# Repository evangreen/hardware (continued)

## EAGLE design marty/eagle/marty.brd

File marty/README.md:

# Marty McFly

The Marty McFly was a set of boards I created in late 2015 for my girlfriend as a gift. It's an LED countdown clock, in the style of the console from "Back to the Future". The three displays track the programmable "destination time" on the top row, the current time on the bottom row, and the "estimated time to arrival" in the middle row. The destination time and current time can be programmed using the keypad. The ETA counts up if the current time is after the destination time.

### Motivation
Because it's fun. I was hoping to give this to my girlfriend in time for the Back to the Future anniversary, but failed to complete it in time. She still appreciated the gift, and she ended up making the cool backing and framing for it.

I also wanted a chance to play with the HT16K33 chip, which drives a matrix of LEDs with constant current, and can simultaneously scan in a matrix keypad. It interfaces with a microcontroller via I2C.

### Sourcing
I wanted attractive LEDs and a retro keypad for this project. It seems like most of the cheap 7-segment displays being sold now have rectangular bars for the top and bottom segments. I prefer the more symmetric face where all segments have the pointy ends that join with each other. This led me toward the older HDSP LEDs that HP used to make. I also needed a consistent look across three colors: red, yellow and green. It took some doing, but I eventually found sets of LEDs in each color with the front face I wanted. I also stumbled across somebody selling old touchtone phone keypads on eBay, which seemed perfect for this project. Once I had my LEDs, I could start designing the board.

### Hardware Design
I used Seeedstudio to make my boards. They are incredibly cheap, but it takes awhile for the boards to get back to you, and you must buy quantities of at least 5. Rather than making one very large board (which would have been very expensive), or two different types of small boards, I wanted to send away for a single PCB design that could serve multiple purposes, depending on which parts were populated.

Each row in the display is actually two boards side by side, with holes for LEDs in a 2-2-4 digit combination. For the date version on the left, all LEDs are populated, and for the time on the right, the last two digits of the year are left unpopulated.

Most of the boards are simply display boards. Pins on the left pipe I2C commands directly into the HT16K33, and pins on the right forward those commands out to the next board. One board also has an ATMega on it, this is the master board that controls all the other display boards. Of course, the design is the same, so all boards have the traces and pads for the ATMega, but only one has it populated. One board also has the keypad connected to it (though again, the keypad pins are there on every board). I used solder bridge "parts" in the PCB design, then blobbed solder bridges in unique binary combinations to give each board a different I2C ID.

### Firwmare Design
The firmware on the ATMega needs to keep track of the current date and time, store a destination time, calculate the delta between them, and display all three of these values by sending them out to the displays via I2C. It also needs to poll for changes on the keypad, and allow for programming of either the current time or the destination time.

Tracking time is always tricky business. Computing the difference between two calendar dates can also be very tricky, especially when considering changes like Daylight Saving transitions and computing a delta in terms of months and days.

Internally I store time as a tuple of Year, Day (of year), and Second (of day). Storing it this way means I can add and subtract time easily, and only worry about things like Daylight Saving when it's time to display something. Advancing the time is done by adding to the seconds, then calling a normalize function to make sure seconds, days, and year are all within a valid range. The number of seconds per day is always constant (since we adjust for Daylight Saving later), and the number of days in a year is either 365 or 366 depending on the year.

Converting a DATE into a full calendar date involves dealing with Daylight Saving, then splitting out the fields. We compute the Day-of-Year on which the Daylight Saving transitions occur for the given year, and see whether or not our day and time fall within that range. If they do, we add another hour to the seconds and re-normalize. Splitting Day-of-Year into Month and Day is a short loop of subtracting the number of days for each month while possible. Splitting the seconds into hours, minutes, and seconds is simple division.

Computing the difference between dates reuses a lot of the same logic. The delta itself is computed by subtracting each field from its counterpart (ie LeftSeconds - RightSeconds, LeftDays - RightDays, LeftYears - RightYears), and then calling the same normalize and display routines as before. The benefit of this is that the ETA counter will always tick down consistently, even across Daylight Saving transitions. The slight downside is it means the first "month" difference between two dates is always the number of days in January, even if two dates in question are something February 1st and March 1st. This seemed like a decent tradeoff, since it allowed a lot of code reuse and kept the countdown consistent, at the cost of intuitive but sometimes ambiguous month delta results.

### Results
Great success! The project came together smoothly, and my girlfriend did an amazing job with the fit and finish of the display. I was overall quite happy with the HT16K33 chips, they made controlling a large number of LEDs and interfacing with the keypad very simple. The green 7-segment HDSP displays I got on eBay are weaker than I'd like. They are a bit dim, and I can see a ripple from the asymmetric multiplexing of the HT16K33 (since some time slots go to the keypad). I blame the LEDs for this more than the HT16K33, since the symptoms appear isolated to the green LEDs. The yellow LEDs, which are actually newer and came from Lite-On, are my favorite, as they're clear and bright.

I would use the HT16K33 again in future projects. It might be a bit expensive in production, but for small hobby projects like mine it does a great job freeing up the MCU and cutting down on PCB traces. I wish I had used it in the Airlight project.

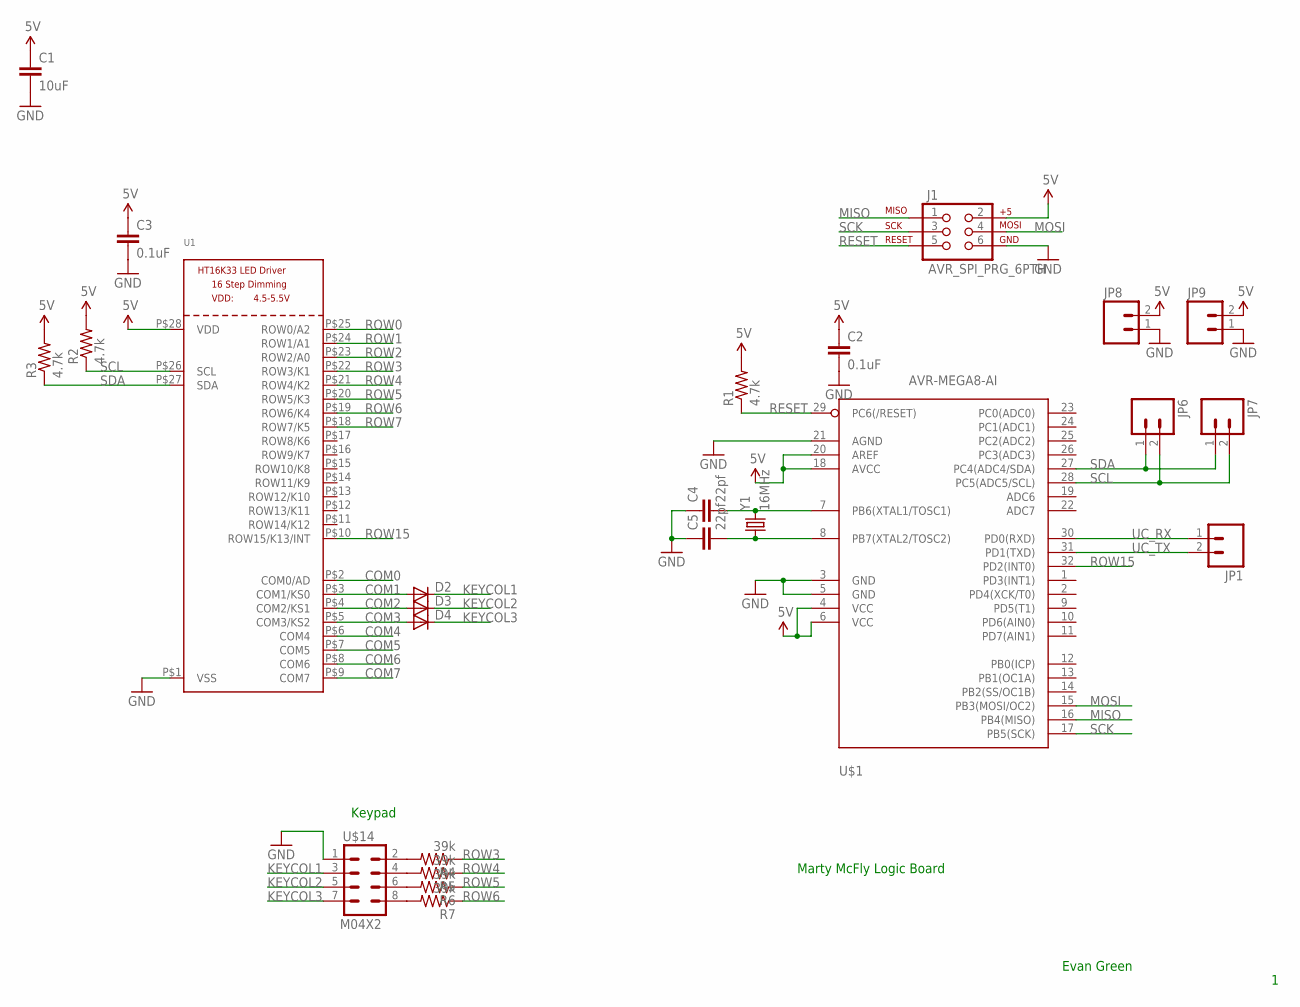
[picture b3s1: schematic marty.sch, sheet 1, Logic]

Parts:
C1: 10uF; 1210
C2, C3: 0.1uF; 0402-CAP
C4, C5: 22pf; 0402-CAP
D2, D3, D4: DIODESOD; SOD-323
J1: AVR_SPI_PRG_6PTH; 2X3
JP1, JP6, JP7, JP8, JP9: M02PTH; 1X02
R1, R2, R3: 4.7k; 0402-RES
R4, R5, R6, R7: 39k; 0402-RES
U1: HT16K33_SOP28; SOP28_300MIL
U$1: AVR-MEGA8-AI; TQFP32-08
U$14: M04X2; 2X4
Y1: 16MHz; HC49US

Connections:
5V: C1.1, C2.1, C3.1, J1.2, JP8.2, JP9.2, R1.2, R2.2, R3.2, U1.P$28 (VDD), U$1.4 (VCC), U$1.6 (VCC), U$1.18 (AVCC), U$1.20 (AREF)
COM0: U1.P$2 (COM0/AD); also elsewhere on the board
COM1: D2.2 (A), U1.P$3 (COM1/KS0); also elsewhere on the board
COM2: D3.2 (A), U1.P$4 (COM2/KS1); also elsewhere on the board
COM3: D4.2 (A), U1.P$5 (COM3/KS2); also elsewhere on the board
COM4: U1.P$6 (COM4); also elsewhere on the board
COM5: U1.P$7 (COM5); also elsewhere on the board
COM6: U1.P$8 (COM6); also elsewhere on the board
COM7: U1.P$9 (COM7); also elsewhere on the board
GND: C1.2, C2.2, C3.2, C4.1, C5.1, J1.6, JP8.1, JP9.1, U1.P$1 (VSS), U$1.3 (GND), U$1.5 (GND), U$1.21 (AGND), U$14.1
KEYCOL1: D2.1 (C), U$14.3
KEYCOL2: D3.1 (C), U$14.5
KEYCOL3: D4.1 (C), U$14.7
MISO: J1.1, U$1.16 (PB4(MISO))
MOSI: J1.4, U$1.15 (PB3(MOSI/OC2))
unnamed: C4.2, U$1.7 (PB6(XTAL1/TOSC1)), Y1.2
unnamed: C5.2, U$1.8 (PB7(XTAL2/TOSC2)), Y1.1
unnamed: R4.2, U$14.2
unnamed: R5.2, U$14.4
unnamed: R6.2, U$14.6
unnamed: R7.2, U$14.8
RESET: J1.5, R1.1, U$1.29 (PC6(/RESET))
ROW0: U1.P$25 (ROW0/A2); also elsewhere on the board
ROW1: U1.P$24 (ROW1/A1); also elsewhere on the board
ROW2: U1.P$23 (ROW2/A0); also elsewhere on the board
ROW3: R4.1, U1.P$22 (ROW3/K1); also elsewhere on the board
ROW4: R5.1, U1.P$21 (ROW4/K2); also elsewhere on the board
ROW5: R6.1, U1.P$20 (ROW5/K3); also elsewhere on the board
ROW6: R7.1, U1.P$19 (ROW6/K4); also elsewhere on the board
ROW7: U1.P$18 (ROW7/K5); also elsewhere on the board
ROW15: U1.P$10 (ROW15/K13/INT), U$1.32 (PD2(INT0))
SCK: J1.3, U$1.17 (PB5(SCK))
SCL: JP6.2, JP7.2, R2.1, U1.P$26 (SCL), U$1.28 (PC5(ADC5/SCL))
SDA: JP6.1, JP7.1, R3.1, U1.P$27 (SDA), U$1.27 (PC4(ADC4/SDA))
UC_RX: JP1.1, U$1.30 (PD0(RXD))
UC_TX: JP1.2, U$1.31 (PD1(TXD))

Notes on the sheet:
Marty McFly Logic Board
Evan Green
Keypad

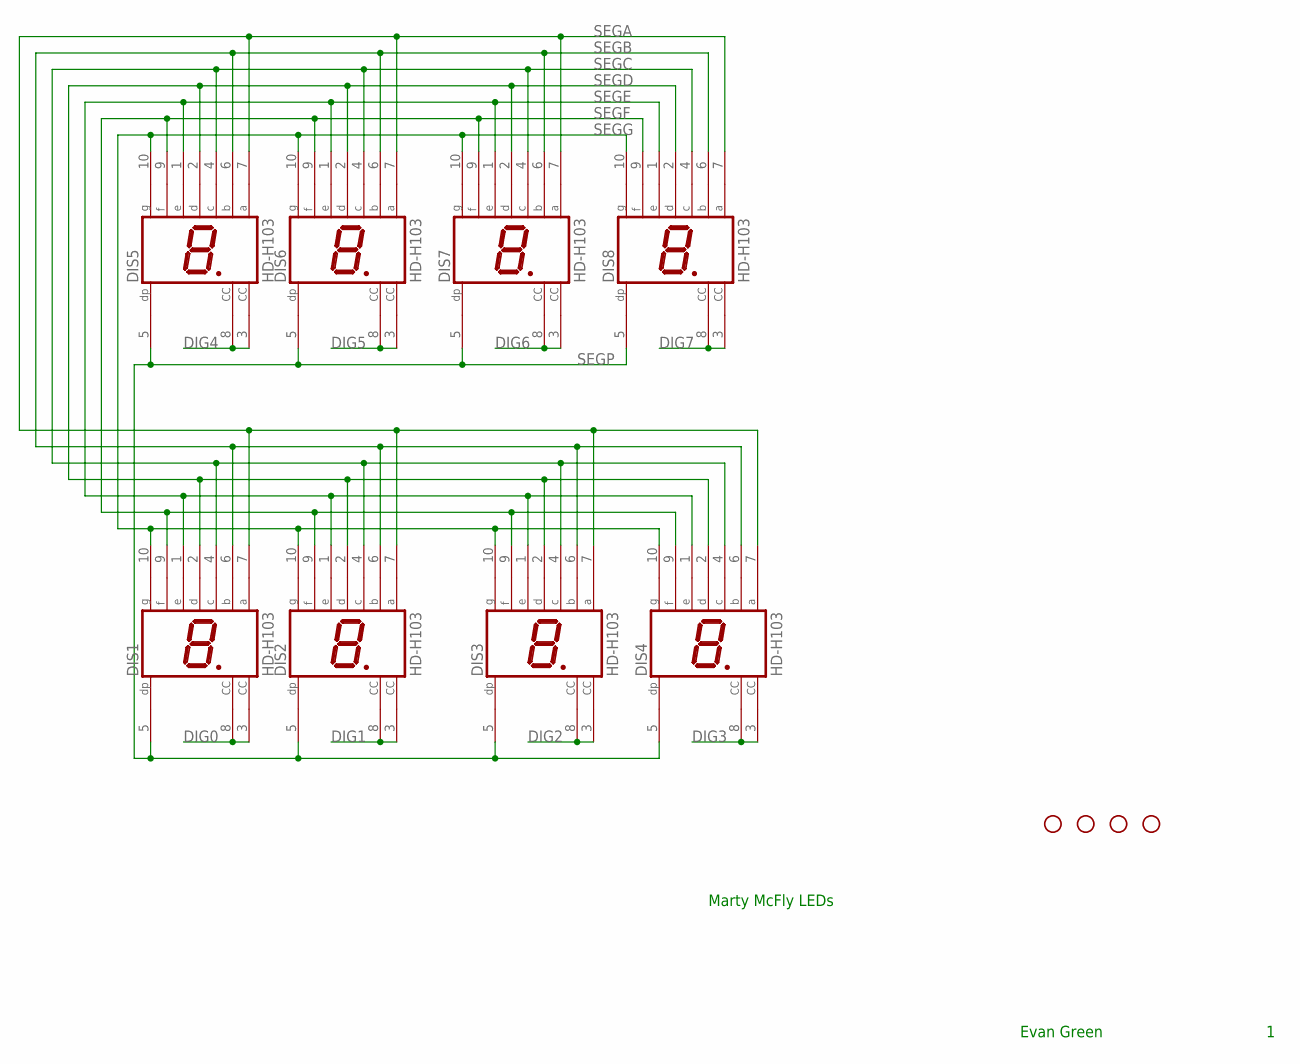
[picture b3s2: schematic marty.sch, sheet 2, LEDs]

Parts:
DIS1, DIS2, DIS3, DIS4, DIS5, DIS6, DIS7, DIS8: HD-H103; HDSP-M
JP2, JP3, JP4, JP5: STAND-OFF

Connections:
DIG0: DIS1.3 (CC), DIS1.8 (CC); also elsewhere on the board
DIG1: DIS2.3 (CC), DIS2.8 (CC); also elsewhere on the board
DIG2: DIS3.3 (CC), DIS3.8 (CC); also elsewhere on the board
DIG3: DIS4.3 (CC), DIS4.8 (CC); also elsewhere on the board
DIG4: DIS5.3 (CC), DIS5.8 (CC); also elsewhere on the board
DIG5: DIS6.3 (CC), DIS6.8 (CC); also elsewhere on the board
DIG6: DIS7.3 (CC), DIS7.8 (CC); also elsewhere on the board
DIG7: DIS8.3 (CC), DIS8.8 (CC); also elsewhere on the board
SEGA: DIS1.7 (A), DIS2.7 (A), DIS3.7 (A), DIS4.7 (A), DIS5.7 (A), DIS6.7 (A), DIS7.7 (A), DIS8.7 (A); also elsewhere on the board
SEGB: DIS1.6 (B), DIS2.6 (B), DIS3.6 (B), DIS4.6 (B), DIS5.6 (B), DIS6.6 (B), DIS7.6 (B), DIS8.6 (B); also elsewhere on the board
SEGC: DIS1.4 (C), DIS2.4 (C), DIS3.4 (C), DIS4.4 (C), DIS5.4 (C), DIS6.4 (C), DIS7.4 (C), DIS8.4 (C); also elsewhere on the board
SEGD: DIS1.2 (D), DIS2.2 (D), DIS3.2 (D), DIS4.2 (D), DIS5.2 (D), DIS6.2 (D), DIS7.2 (D), DIS8.2 (D); also elsewhere on the board
SEGE: DIS1.1 (E), DIS2.1 (E), DIS3.1 (E), DIS4.1 (E), DIS5.1 (E), DIS6.1 (E), DIS7.1 (E), DIS8.1 (E); also elsewhere on the board
SEGF: DIS1.9 (F), DIS2.9 (F), DIS3.9 (F), DIS4.9 (F), DIS5.9 (F), DIS6.9 (F), DIS7.9 (F), DIS8.9 (F); also elsewhere on the board
SEGG: DIS1.10 (G), DIS2.10 (G), DIS3.10 (G), DIS4.10 (G), DIS5.10 (G), DIS6.10 (G), DIS7.10 (G), DIS8.10 (G); also elsewhere on the board
SEGP: DIS1.5 (DP), DIS2.5 (DP), DIS3.5 (DP), DIS4.5 (DP), DIS5.5 (DP), DIS6.5 (DP), DIS7.5 (DP), DIS8.5 (DP); also elsewhere on the board

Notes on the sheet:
Marty McFly LEDs
Evan Green

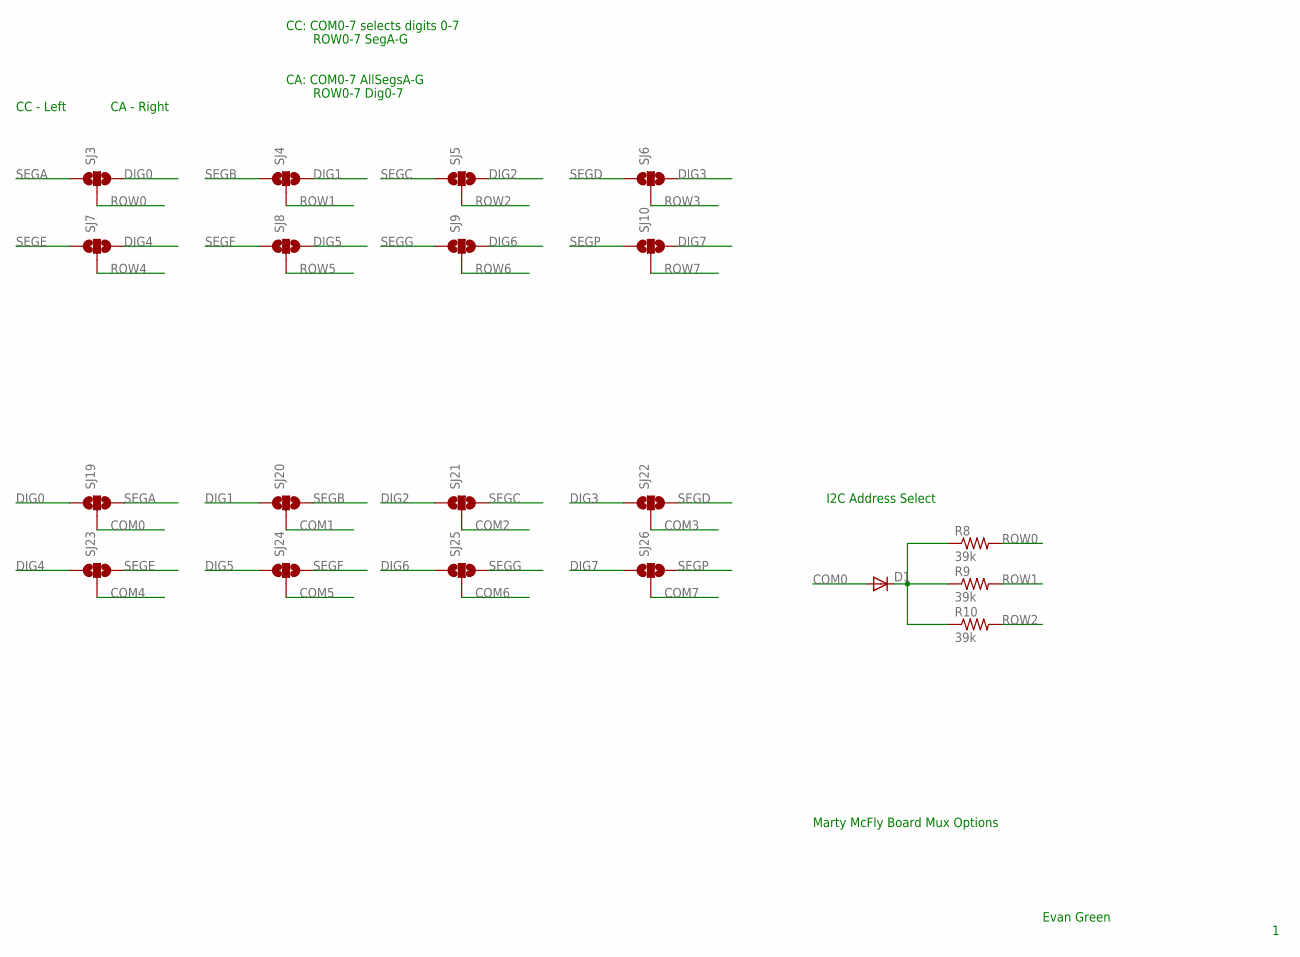
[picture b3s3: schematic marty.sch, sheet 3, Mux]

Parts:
D1: DIODESOD; SOD-323
R8, R9, R10: 39k; 0402-RES
SJ3, SJ4, SJ5, SJ6, SJ7, SJ8, SJ9, SJ10, SJ19, SJ20, SJ21, SJ22, SJ23, SJ24, SJ25, SJ26: SOLDERJUMPER_2WAYS; SJ_3

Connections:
COM0: D1.2 (A), SJ19.2; also elsewhere on the board
COM1: SJ20.2; also elsewhere on the board
COM2: SJ21.2; also elsewhere on the board
COM3: SJ22.2; also elsewhere on the board
COM4: SJ23.2; also elsewhere on the board
COM5: SJ24.2; also elsewhere on the board
COM6: SJ25.2; also elsewhere on the board
COM7: SJ26.2; also elsewhere on the board
DIG0: SJ3.3, SJ19.1; also elsewhere on the board
DIG1: SJ4.3, SJ20.1; also elsewhere on the board
DIG2: SJ5.3, SJ21.1; also elsewhere on the board
DIG3: SJ6.3, SJ22.1; also elsewhere on the board
DIG4: SJ7.3, SJ23.1; also elsewhere on the board
DIG5: SJ8.3, SJ24.1; also elsewhere on the board
DIG6: SJ9.3, SJ25.1; also elsewhere on the board
DIG7: SJ10.3, SJ26.1; also elsewhere on the board
unnamed: D1.1 (C), R8.1, R9.1, R10.1
ROW0: R8.2, SJ3.2; also elsewhere on the board
ROW1: R9.2, SJ4.2; also elsewhere on the board
ROW2: R10.2, SJ5.2; also elsewhere on the board
ROW3: SJ6.2; also elsewhere on the board
ROW4: SJ7.2; also elsewhere on the board
ROW5: SJ8.2; also elsewhere on the board
ROW6: SJ9.2; also elsewhere on the board
ROW7: SJ10.2; also elsewhere on the board
SEGA: SJ3.1, SJ19.3; also elsewhere on the board
SEGB: SJ4.1, SJ20.3; also elsewhere on the board
SEGC: SJ5.1, SJ21.3; also elsewhere on the board
SEGD: SJ6.1, SJ22.3; also elsewhere on the board
SEGE: SJ7.1, SJ23.3; also elsewhere on the board
SEGF: SJ8.1, SJ24.3; also elsewhere on the board
SEGG: SJ9.1, SJ25.3; also elsewhere on the board
SEGP: SJ10.1, SJ26.3; also elsewhere on the board

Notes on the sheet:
Marty McFly Board Mux Options
Evan Green
CC - Left
CA - Right
CC: COM0-7 selects digits 0-7
ROW0-7 SegA-G
CA: COM0-7 AllSegsA-G
ROW0-7 Dig0-7
I2C Address Select

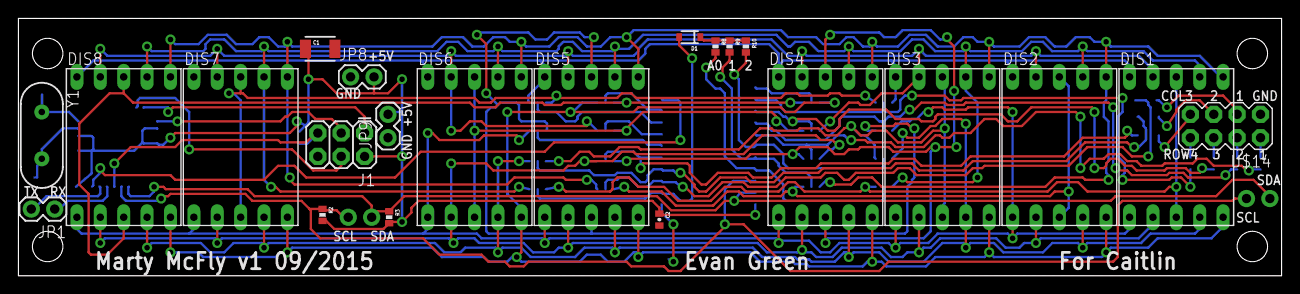
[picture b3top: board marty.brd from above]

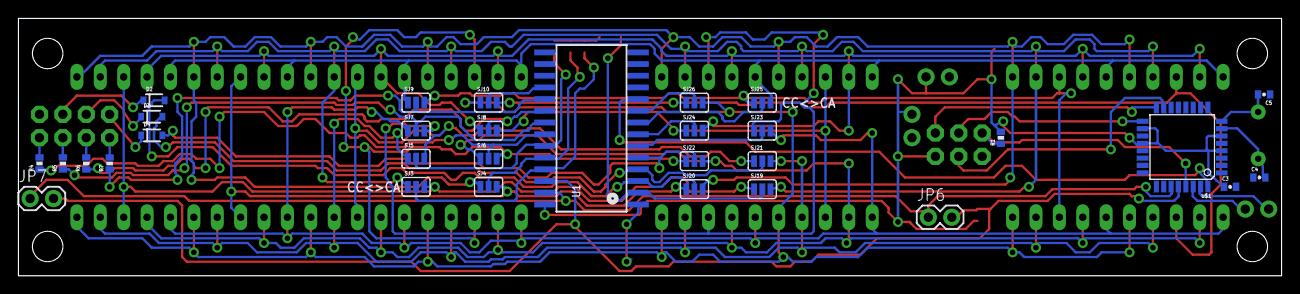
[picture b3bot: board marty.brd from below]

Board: 2 copper layers, 137.2 x 27.9 mm, 57 parts (31 on the bottom side), 53 nets.

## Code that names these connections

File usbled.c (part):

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
// ----------------------------------------------------------------------
// Programmer output pins:
//    LED    PB0    (D0)
#define LED PB0
//    VCC    PB1    (D1)
//    VCC    PB2    (D2)
//    VCC    PB3    (D3)
//    RESET    PB5    (D4)
#define RESET PB4
//    MOSI    PB5    (D5)
#define MOSI  PB5
//    SCK    PB7    (D7)
#define SCK   PB7

// ----------------------------------------------------------------------
#define    PORT        PORTB
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
// ----------------------------------------------------------------------
// Programmer input pins:
//    MISO    PB6
#define MISO       6
// ----------------------------------------------------------------------
#define    PIN        PINB
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
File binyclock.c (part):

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// Define bits off of port C.
//

#define ROW3 (1 << 1)
#define ROW5 (1 << 4)
#define ROW6 (1 << 3)
#define ROW7 (1 << 2)
#define COLUMN1 (1 << 0)
#define COLUMN2 (1 << 5)
#define PORTC_OFF_VALUE (COLUMN1 | COLUMN2)
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// Define bits off of port D.
//

#define ROW1 (1 << 5)
#define ROW2 (1 << 4)
#define ROW4 (1 << 0)
#define COLUMN3 (1 << 3)
#define COLUMN4 (1 << 2)
#define COLUMN5 (1 << 1)
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
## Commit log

2010-11-11 Skeleton implementation.
2010-11-15 Added the Game of Life and Sokoban.
2010-11-20 Added Tetris.
2010-11-24 Added clock applet and font data.
2011-01-10 Initial revision, for Caitlin.
2011-01-16 Make some tweaks, and add EEPROM functionality.
2011-01-20 Version for Jason
2011-03-11 Move mainboard firmware to its own directory.
2011-03-11 Add slave board implementation.
2011-07-07 Initial codebase, the AVR pocket programmer from sparkfun with a custom Makefile.
2011-07-12 Successfully set up USB communication with INT1 line.
2011-07-13 Move the USB interrupt over to the Pin Change Interrupt.
2011-07-14 Bring LEDs online.
2011-07-14 Move to new Device ID.
2011-07-14 Move firmware to its own directory.
2011-07-14 Added LibUSB driver.
2011-07-15 Created basic app.
2011-07-16 Remove old firmware remnants, and create basic version of the app that works on Windows.
2011-07-17 Made the app's features stackable, and added firmware support for the USB LED non-mini version.
2011-07-19 Increase retry delay.
2011-07-20 Build on linux (Ubuntu). Implemented per-CPU usage feature on linux.
2011-07-21 Added the rest of OS support for linux.
2011-07-21 Added Mac OS X support.
2011-07-21 Add mac OS X drivers (libUSB installer).
2011-09-12 Minor fixes for the new boards.
2011-09-12 Move usbled files to their own directory.
2011-09-12 Copy the USBLED firmware over to USBRelay.
2011-09-12 Initial firmware prototype.
2011-09-13 USB Relay initial app and firmware tweaks.
2011-10-03 Switch VID/PID, and add support for serial numbers.
2011-10-03 Fix minor signedness compiler complaint.
2011-10-26 Add stdin and exit-immediately support to usbled.
2011-10-27 Fix exit-immediately option.
2012-01-16 Added -e and return value to usbrelay.
2012-05-20 Remove unused variables.
2012-06-16 Commit a bunch of code from late 2010. Not sure what state it's currently in.
2012-07-04 Add hardware files.
2012-07-04 Added hardware files.
2012-07-04 Added custom library.
2012-07-04 Created empty eagle directory.
2012-07-11 Commit initial revision of custom library and SparkFun resoures.
2012-12-02 Add Toilet Paper light firmware :)
2012-12-22 Added BOM and beginning of casing.
2013-02-17 Import project straight from https://github.com/SFE-Jordan/Sparkfun_32U4_Breakout_Board/ Commit fa0b8e50bda186e2e1b24625401a1ab11e303dfe.
2013-02-17 Add LUFA zip as specified in LUFA readme.txt.
2013-02-17 Remove LUFA, as I didnt read the instructions carefully enough.
2013-02-17 Re-add LUFA, hopefully correctly this time.
2013-02-21 Copied sparkfun-virtualserial example to a new folder.
2013-03-06 Initial version of the app and firmware.
2013-03-06 Remove binary files.
2013-03-06 Add ignore property for the app directory.
2013-03-21 Wired up dashboard functionality.
2013-08-06 Turn on all lights at powerup.
2013-09-29 Add long lost usbrelay schematic files.
2013-11-21 Added newer libraries.
2013-11-21 v1 of Airlight and Airrelay boards.
2013-11-21 Added Excel BOM.
2014-01-15 Skeletal work-in-progress firmware.
2014-01-19 Adding some untested controller code, reappropriated from 2008 independent work.
2014-01-23 Added I/O to the windows test app, and some support firmware for the airlight.
2014-01-27 Feature complete firmware. Still something causing the mainboard to hang when idle.
2014-02-03 Fix firmware hang caused by torn timer read, and clean out dead code.
2014-03-02 Firmware bug fixes.
2015-01-16 Added PDFs and minor formatting changes.
2015-04-21 Added RFM22B docs.
2015-09-15 Added microbuilder library for HT16K33.
2015-09-15 Added some test firmware code for the Marty project.
2015-09-21 Added Marty McFly v1 schematic and board.
2015-09-26 Marty board v1 final.
2015-12-20 Added some very work-in-progress firmware.
2016-01-18 Completed Marty McFly firmware.
2016-01-18 Added partial Rokit KRK RP10S amplifier board schematic.
2016-01-18 Updated preferences.
2016-01-18 Moved airlight files into their own directory.
2016-01-18 Moved binyclock files to their own directory.
2016-01-18 Moved hwlib files to their own directory.
2016-01-18 Moved matrix files to their own directory.
2016-01-18 Moved pcdash files to their own folder.
2016-05-01 Style cleanup on RFM22 code.
2016-05-01 Bug fixes and improvements to airlight firmware.
    1. Added a checksum word to the airlight EEPROM, which seems to get
    occasional byte corruptions.
    2. Added a controller bit to add some randomization to the timing, which
    makes things more interesting.
    3. Moved to DWARF symbols from STABS, since my debugger can now handle it.
    4. Fixed a bug in the controller logic that was causing phase 4 to never
2016-11-18 Skeleton project for icegrid.
    This is my first project with the STM32F103. I got these little boards and
    a programmer for $2 each off eBay. They feature an ARM Cortex M3, USB, and
    a whole boatload of peripherals.
    Took me a little while to get the tools up and running, but so far I'm
    quite impressed. This project is a bare bones one that just blinks the
    on-board LED. It uses our arm-none-minoca GCC toolchain.
2016-12-10 Fired up the timer (TIM4).
    TIM4 is now outputting the "high" PWM signal all the time.
2017-01-21 Icegrid: Got the WS2812 LED strip under control.
2017-01-30 Icegrid: Some initial Wifi connection server code.
    This code (sometimes) exposes a wifi server that will collect credentials.
    It currently does not read out the POST parameters, and seems to not
    succeed on the first connection attempt.
    Next up is to read the POST parameters, save the connection somewhere, and
    attempt a client connection. Also figure out why requests seem to
    sometimes fail.
2017-02-04 Add libaeabi-cortexm0.
    The HAL_FLASH module uses __aeabi_llsr because it takes in a 64-bit datum
    and shifts it. Add those compiler intrinsics via a nice library I found on
    the internet. Many thanks to Jorg Mische for the library.
2017-02-04 Finished first iteration of icegrid firmware.
    This firmware starts as an AP for one minute to allow for wireless
    configuration. If it gets a valid configuration, it saves that into flash,
    and then connects to that wifi network. From there, it forever receives
    UDP requests on port 8080 that change the LEDs.
2017-02-04 Random unknown changes from the airlight project.
    These changes have been sitting in my directory for some time. I don't
    know if the one actual change (a new 5 second delay) is actually needed or
    not.
2017-02-27 Icegrid: Continue to print IP until someone connects.
    The icegrid should continue to print out its IP address until someone
    connects to it. Before this it just printed it once, and if you missed it
    you had to power cycle it.
2017-02-27 Airlight: Change 5 second delay to 1 second.
    I'm not sure a delay is necessary at all, but 5 seconds is way too much.
2017-02-27 Binyclock: Change it back to Caitlin :)
2017-03-05 Added wunderground API connection.
    The IceGrid now shows the 5-day weather forecast for three cities!
2017-03-05 Make icegrid weather.py live.
    Now it hits the API rather than grabbing old data from a file.
2017-03-05 Icegrid: update every hour.
    Wunderground give you 500 calls a day. Live a little and update every hour
    for a grand 72 calls per day.
2017-03-06 Weather.py: forgot to add 'snow' to 'snow'.
2017-03-12 Random fixes to pcdash.
    It's been awhile since PCdash was compiled. Fixed a couple of build
    issues, and made the makefile for sh rather than cmd.
2017-04-22 Minor tweaks to icegrid.
    Fixed a missing newline, and added the Template.docx file I was playing
    with.
2017-04-22 Add a project wide .gitignore.
    This ignores .a and .o files project-wide.
2017-04-22 Initial revision of the AudiDash firmware.
    This firmware, which runs on the STM32F1 microcontrollers, controls a 1998
    Audi A4 instrument cluster. It uses a "blue pill" STM32F1 board (super
    cheap on eBay) and an ESP8266 Wifi board. It will beam out a network for
    the first 60 seconds after being powered on, which you can connect to to
    set the real WiFi credentials. These settings will be stored in the flash
    for future power-ups, though there will still be a 60 second period in AP
2017-04-22 Refactored STM32F1 files into a common folder.
    Rather than the AudiDash reaching over into the IceGrid project, now
    there's a top level stm32f1 folder that both projects can draw from.
2017-05-03 Add beginnings of an AudiDash app.
    This change copies pcdash over to the audidash directory, modifies it to
    use a socket rather than a serial port, and gets debug mode working.
    Theoretically. Right now all I know is that it compiles and debug mode
    seems to interact the way it should.
2017-05-15 AudiDash: Calibrated gauges and wired up the app.
    The gauges and indicators are now wired up to various inputs and controls
    within Windows. The oil gauge is network usage, the fuel gauge is disk
    usage, and the temperature gauge is usage time. The RPMs correspond to
    mouse clicks, and the speed correlates to WPM typing.
2017-05-15 Minor bug fix to AudiDash.
    One of the indicators had the wrong bit in the app. Fast fingers...
2017-05-24 Audidash bug fixes.
    Fixed a wrong port, and an integer overflow.
2017-06-27 Icegrid: Darkness please between midnight and 7AM.
2017-09-19 Add pictures! And the start of a couple descriptions.
    This repository would really be a lot more fun with some pictures of the
    projects I've done and some writeups for context. Here are the pictures,
    and I started working on the writeups in NY. More to come later.
2017-09-24 Add a couple more READMEs, going alphabetically.
    This is useful and I'm glad I'm doing it, but I wish I had done them as I
    went along. Note to self: add READMEs earlier in future projects.
2017-09-24 More READMEs. Only two more to go.
2017-09-25 Add the last individual READMEs.
    Next up is to create a main README, add a table of contents, and link in
    the pictures.
2017-09-26 Add LICENSE file.
    Licensed under GPLv3 (only).
2017-09-26 Add root level README.
2017-09-26 Markdown fixes.
2017-09-26 Add thumbnails to main README.
    This change adds smaller thumbnails for the main page, and adds the image
    links to the airlight README. If this goes well, I'll add the other images
    to the other READMEs, but I need to see what it looks like on GitHub
    first.
2017-09-26 Try non-list formatting on the main README.
    This change tries different formatting for the main README project list,
    and adds photos to the individual project READMEs.
2017-09-26 Spacing fixes to the README images.
    Blank lines are needed, otherwise the images and texts just continue to
    the right.
